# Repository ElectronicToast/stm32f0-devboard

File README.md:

# stm32f0-devboard

A minimal development board featuring an STM32F030C8T6

## Description
This is a minimal development board for STM32F0xxC MCUs designed for ease of turnkey assembly by JLCPCB Co. Ltd. The board includes HSE and LSE oscillators, reset and user button, power and user LED, BOOT0 boot mode select solder jumper, and a SWD programming header. All components, sans connectors, can be assembled by JLCPCB, and tooling holes for the SMT assembly process are provided.

## Licensing
This project is released under the terms of the MIT License.

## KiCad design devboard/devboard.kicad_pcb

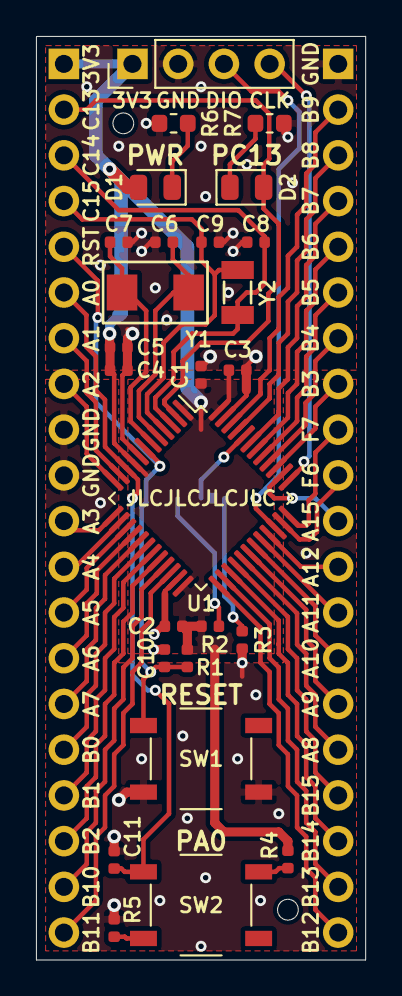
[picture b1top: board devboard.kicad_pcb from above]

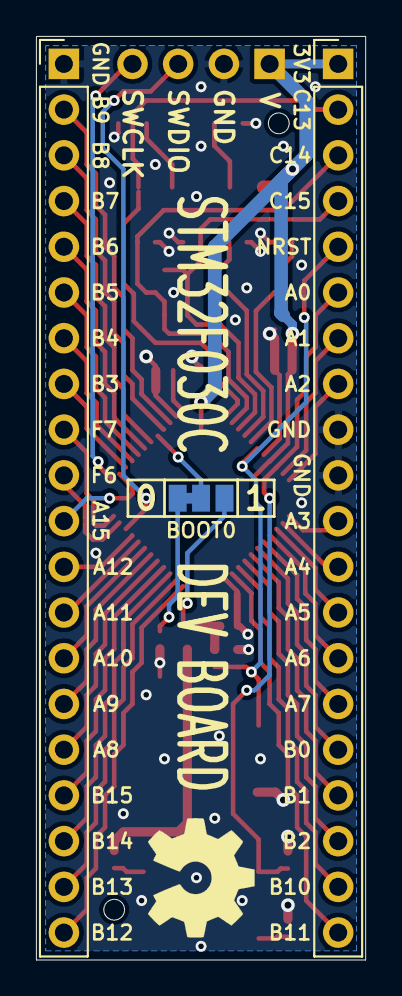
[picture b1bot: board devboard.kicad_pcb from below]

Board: 2 copper layers, 18.3 x 51.3 mm, 29 parts (3 on the bottom side), 48 nets.

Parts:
C1: 4.7uF; C_0402_1005Metric
C2, C3, C10, C11: 0.1uF; C_0402_1005Metric
C4: 10nF; C_0402_1005Metric
C5: 1uF; C_0402_1005Metric
C6, C7: 33pF; C_0402_1005Metric
C8, C9: 18pF; C_0402_1005Metric
D1: RED; LED_0805_2012Metric
D2: BLUE; LED_0805_2012Metric
J1, J2: PinHeader_0.1_01x20; PinHeader_1x20_P2.54mm_Vertical
J3: PinHeader_0.1_01x04; PinHeader_1x04_P2.54mm_Vertical
JP1: SJ3; SolderJumper-3_P1.3mm_Bridged12_Pad1.0x1.5mm_NoMark
R1, R2, R3, R4: 10K; R_0402_1005Metric
R5: 100; R_0402_1005Metric
R6: 510; R_0603_1608Metric
R7: 330; R_0603_1608Metric
SW1, SW2: TS-1187A-C-C-B; SW_Push_PTS526
U1: STM32F030C8T6; LQFP-48_7x7mm_P0.5mm
Y1: 8MHz; Crystal_X50328MSB2GI
Y2: 32.768kHz; Crystal_Q13FC1350000400

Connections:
/BOOT0: JP1.2, U1.44
/HSE_IN: C6.1, U1.5, Y1.1
/HSE_OUT: C7.1, U1.6, Y1.2
/LSE_IN: C8.1, J1.3, U1.3, Y2.1
/LSE_OUT: C9.1, J1.4, U1.4, Y2.2
/PA0: C11.2, J1.6, R4.1, SW2.1, U1.10
/PA1: J1.7, U1.11
/PA2: J1.8, U1.12
/PA3: J1.11, U1.13
/PA4: J1.12, U1.14
/PA5: J1.13, U1.15
/PA6: J1.14, U1.16
/PA7: J1.15, U1.17
/PA8: J2.16, U1.29
/PA9: J2.15, U1.30
/PA10: J2.14, U1.31
/PA11: J2.13, U1.32
/PA12: J2.12, U1.33
/PA15: J2.11, U1.38
/PB0: J1.16, U1.18
/PB1: J1.17, U1.19
/PB2: J1.18, U1.20
/PB3: J2.8, U1.39
/PB4: J2.7, U1.40
/PB5: J2.6, U1.41
/PB6: J2.5, U1.42
/PB7: J2.4, U1.43
/PB8: J2.3, U1.45
/PB9: J2.2, U1.46
/PB10: J1.19, U1.21
/PB11: J1.20, U1.22
/PB12: J2.20, U1.25
/PB13: J2.19, U1.26
/PB14: J2.18, U1.27
/PB15: J2.17, U1.28
/PC13: D2.2, J1.2, U1.2
/PF6: J2.10, U1.35
/PF7: J2.9, U1.36
/SWCLK: J3.4, U1.37
/SWDIO: J3.3, U1.34
/~RESET: C10.2, J1.5, R1.1, SW1.1, U1.7
GND: C1.2, C2.2, C3.2, C4.2, C5.2, C6.2, C7.2, C8.2, C9.2, C10.1, C11.1, J1.9, J1.10, J2.1, J3.2, R3.2, R5.1, R6.1, R7.1, SW1.2, U1.8, U1.23, U1.47
unnamed: D1.1, R6.2
unnamed: D2.1, R7.2
unnamed: JP1.1, R3.1
unnamed: JP1.3, R2.1
unnamed: R5.2, SW2.2
VDD: C1.1, C2.1, C3.1, C4.1, C5.1, D1.2, J1.1, J3.1, R1.2, R2.2, R4.2, U1.1, U1.9, U1.24, U1.48

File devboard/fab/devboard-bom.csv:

Comment,Designator,Footprint, LCSC Part#
4.7uF,C1,0402_C,C23733
100nF,"C2,C3,C10,C11",0402_C,C1525
10nF,C4,0402_C, C15195
1uF,C5,0402_C,C52923
33pF,"C6,C7",0402_C,C1562
18pF,"C8,C9",0402_C,C1549
FC-2012HRK-620D Red 0603,D1,0805_LED,C84256
C2293 Blue LED,D2,0805_LED,C2293
10K,"R2,R3,R1,R4",0402_R, C25744
100,R5,0402_R, C25076
510,R6,0603_R,C23193
330,R7,0603_R,C23138
TS-1187A-C-C-B,"SW1,SW2",SW-4_5.1x5.1x1.7,C318889
STM32F030C8T6,U1,LQFP48,C23922
X50328MSB2GI 8MHz,Y1,SMD-5032_2P,C115962
Q13FC1350000400 32.768kHz,Y2,SMD-3215_2P,C32346

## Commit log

2020-07-16 Add files
2020-12-24 Add images
